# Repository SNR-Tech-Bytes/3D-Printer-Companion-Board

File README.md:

# 3D-Printer-Companion-Board
3D Printer Companion Board for voltage regulation and enclosure interface
For more information watch this video: https://youtu.be/JjFgt_RT7m0

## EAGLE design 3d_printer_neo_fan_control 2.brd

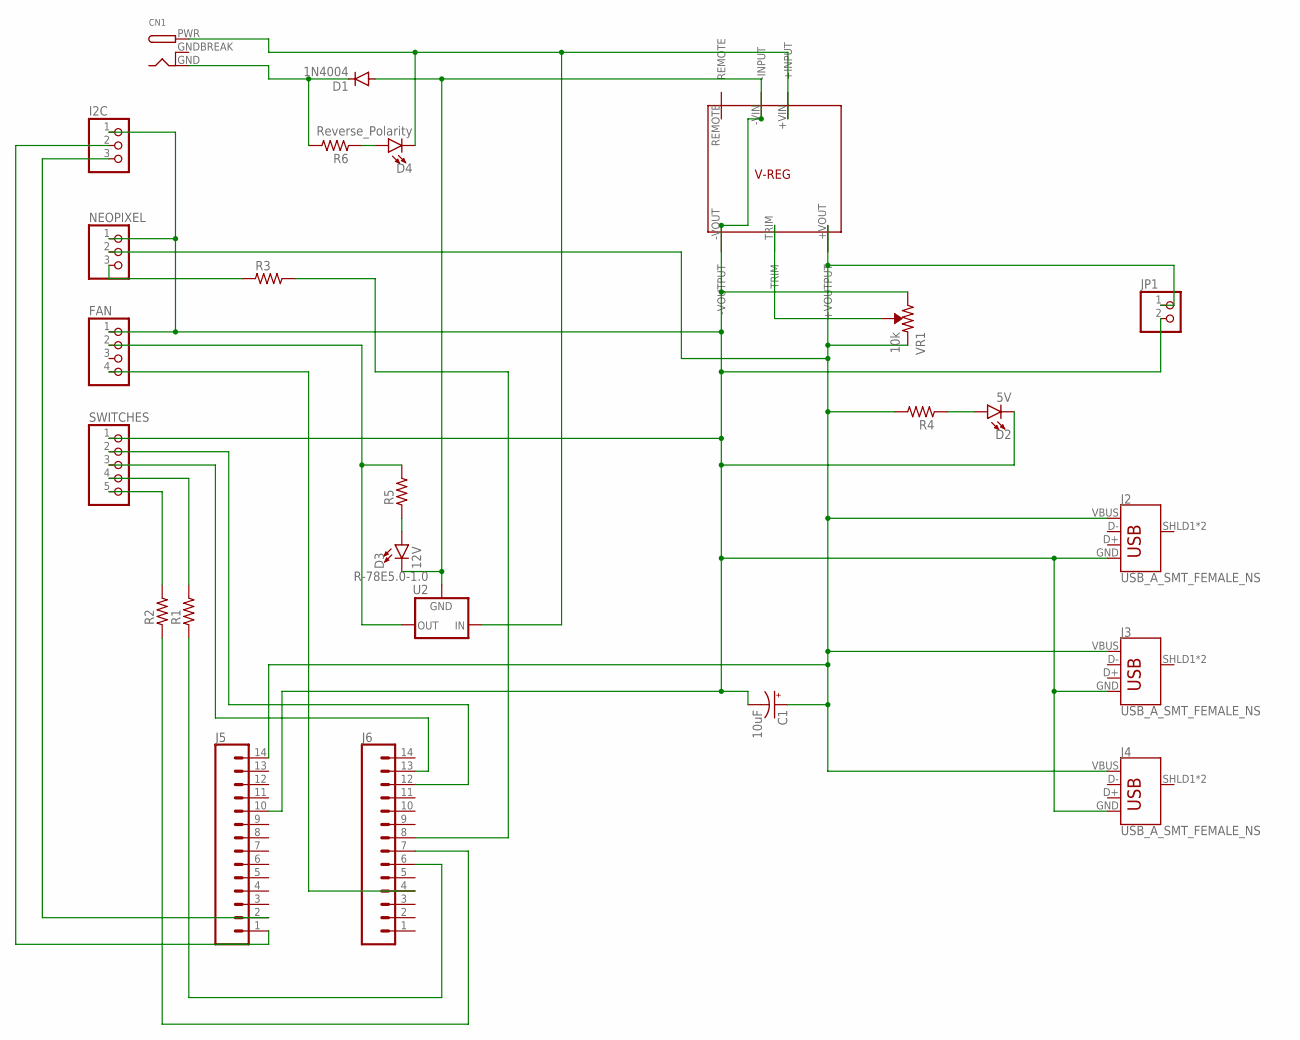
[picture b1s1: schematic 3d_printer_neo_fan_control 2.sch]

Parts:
C1: 10uF; CPOL-RADIAL-2.5MM-5MM-KIT
CN1: DCBARRELPTH; DCJACK_2MM_PTH
D1: 1N4004; DO41-10
D2: 5V; LED-1206
D3: 12V; LED-1206
D4: Reverse_Polarity; LED-1206
FAN: PINHD-1X4; 1X04
I2C: PINHD-1X3; 1X03
J2, J3, J4: USB_A_SMT_FEMALE_NS; USB-A-S-NOSILK-FEMALE
J5, J6: CONN_14; 1X14
JP1: PINHD-1X2; 1X02
NEOPIXEL: PINHD-1X3; 1X03
R1, R2, R3, R4, R5, R6: RC-MASTER-SMD_R_1206MP; RC-MASTER-SMD_R1206MP
SWITCHES: PINHD-1X5; 1X05
U2: R-78E5.0-1.0; DC-DC_CONVERTER_78XX
U$1: CINCON-EC4SBW
VR1: 10k; TRIMPOT-SMD-TC33X

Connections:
5V: C1.1 (+), J2.VBUS, J3.VBUS, J4.VBUS, J5.14, JP1.1, NEOPIXEL.2, R4.2, U$1.+VOUT (+VOUTPUT), VR1.3 (CCW)
5V_GND: C1.2 (-), D1.A, D2.C, D3.C, FAN.1, I2C.1, J2.GND, J3.GND, J4.GND, J5.10, JP1.2, NEOPIXEL.1, SWITCHES.1, U2.GND, U$1.-VIN (-INPUT), U$1.-VOUT (-VOUTPUT), VR1.1 (CW)
12V: FAN.2, R5.2, U2.VOUT (OUT)
DIODE: CN1.GND, D1.C, R6.2
GNDBREAK: CN1.GNDBREAK
unnamed: D3.A, R5.1
unnamed: D4.A, R6.1
unnamed: U$1.TRIM, VR1.2 (WIPER)
unnamed: D2.A, R4.1
unnamed: R2.2, SWITCHES.5
unnamed: FAN.4, J6.4
unnamed: R1.2, SWITCHES.4
unnamed: J6.6, R1.1
unnamed: J6.7, R2.1
unnamed: NEOPIXEL.3, R3.1
unnamed: J6.13, SWITCHES.3
unnamed: J6.12, SWITCHES.2
unnamed: J6.8, R3.2
unnamed: I2C.2, J5.1
unnamed: I2C.3, J5.2
VIN: CN1.PWR, D4.C, U2.VIN (IN), U$1.+VIN (+INPUT)

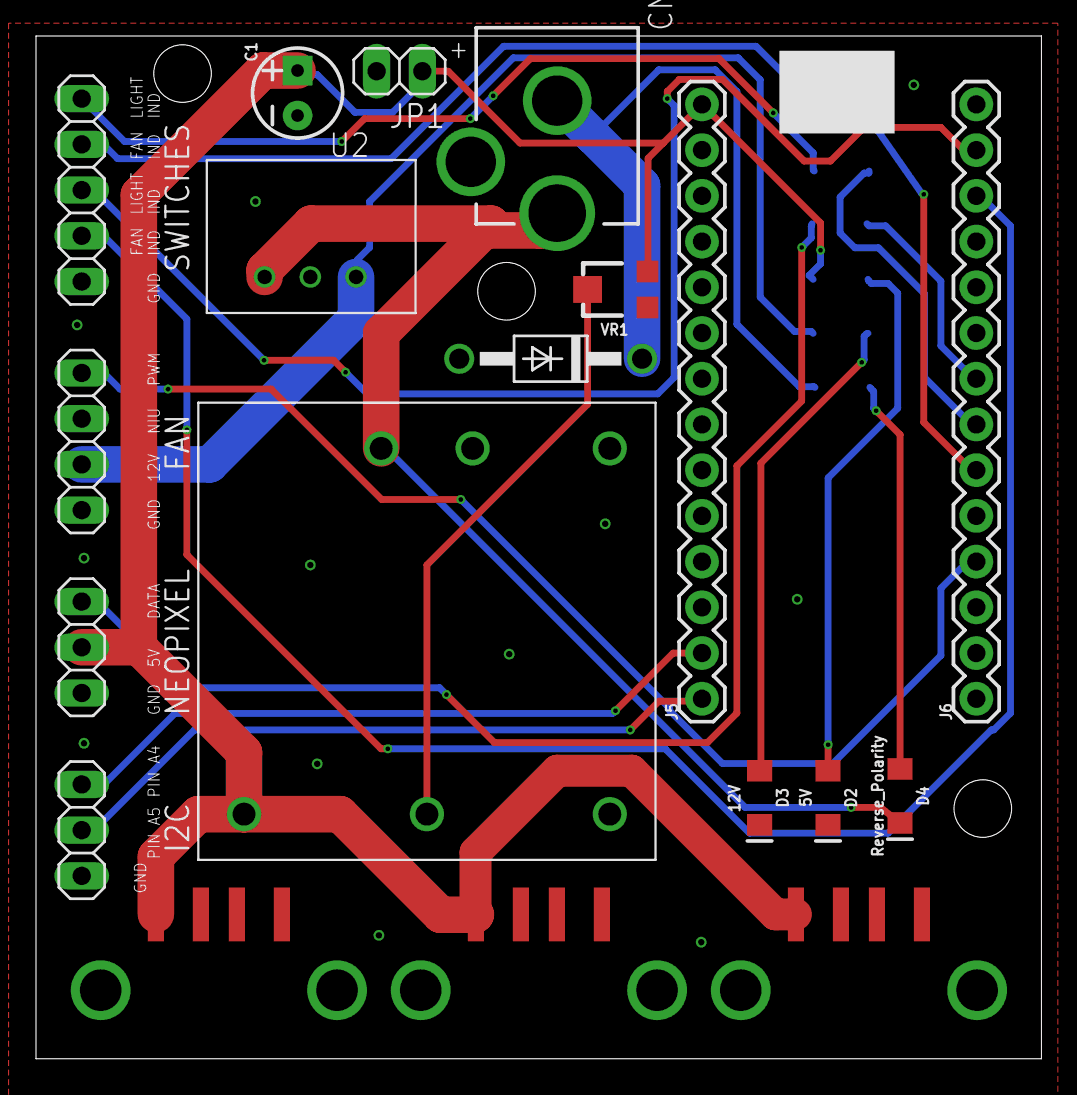
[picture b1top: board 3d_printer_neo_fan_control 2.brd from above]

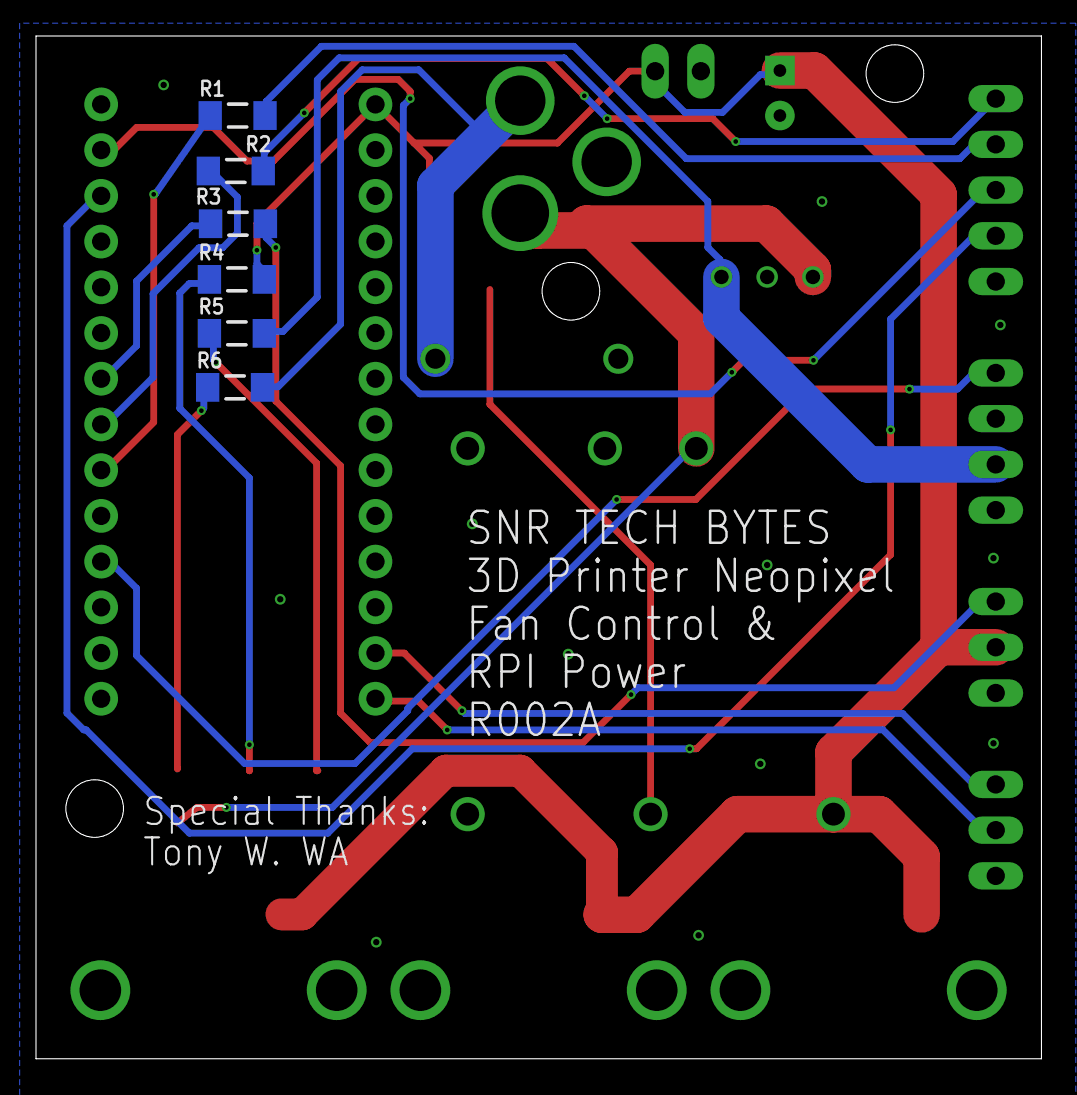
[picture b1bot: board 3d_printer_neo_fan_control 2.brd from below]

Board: 2 copper layers, 55.9 x 56.8 mm, 25 parts (6 on the bottom side), 20 nets.

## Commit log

2021-02-24 eagle brd and sch files added
2021-02-24 Added BOM and board component map
2021-02-24 Added enclosure STL's and Arduino code
2021-02-24 Replaced BRD and SCH with updated files

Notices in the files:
parts and their libraries:
SparkFun-Capacitors: Licensing: Creative Commons ShareAlike 4.0 International - https://creativecommons.org/licenses/by-sa/4.0
